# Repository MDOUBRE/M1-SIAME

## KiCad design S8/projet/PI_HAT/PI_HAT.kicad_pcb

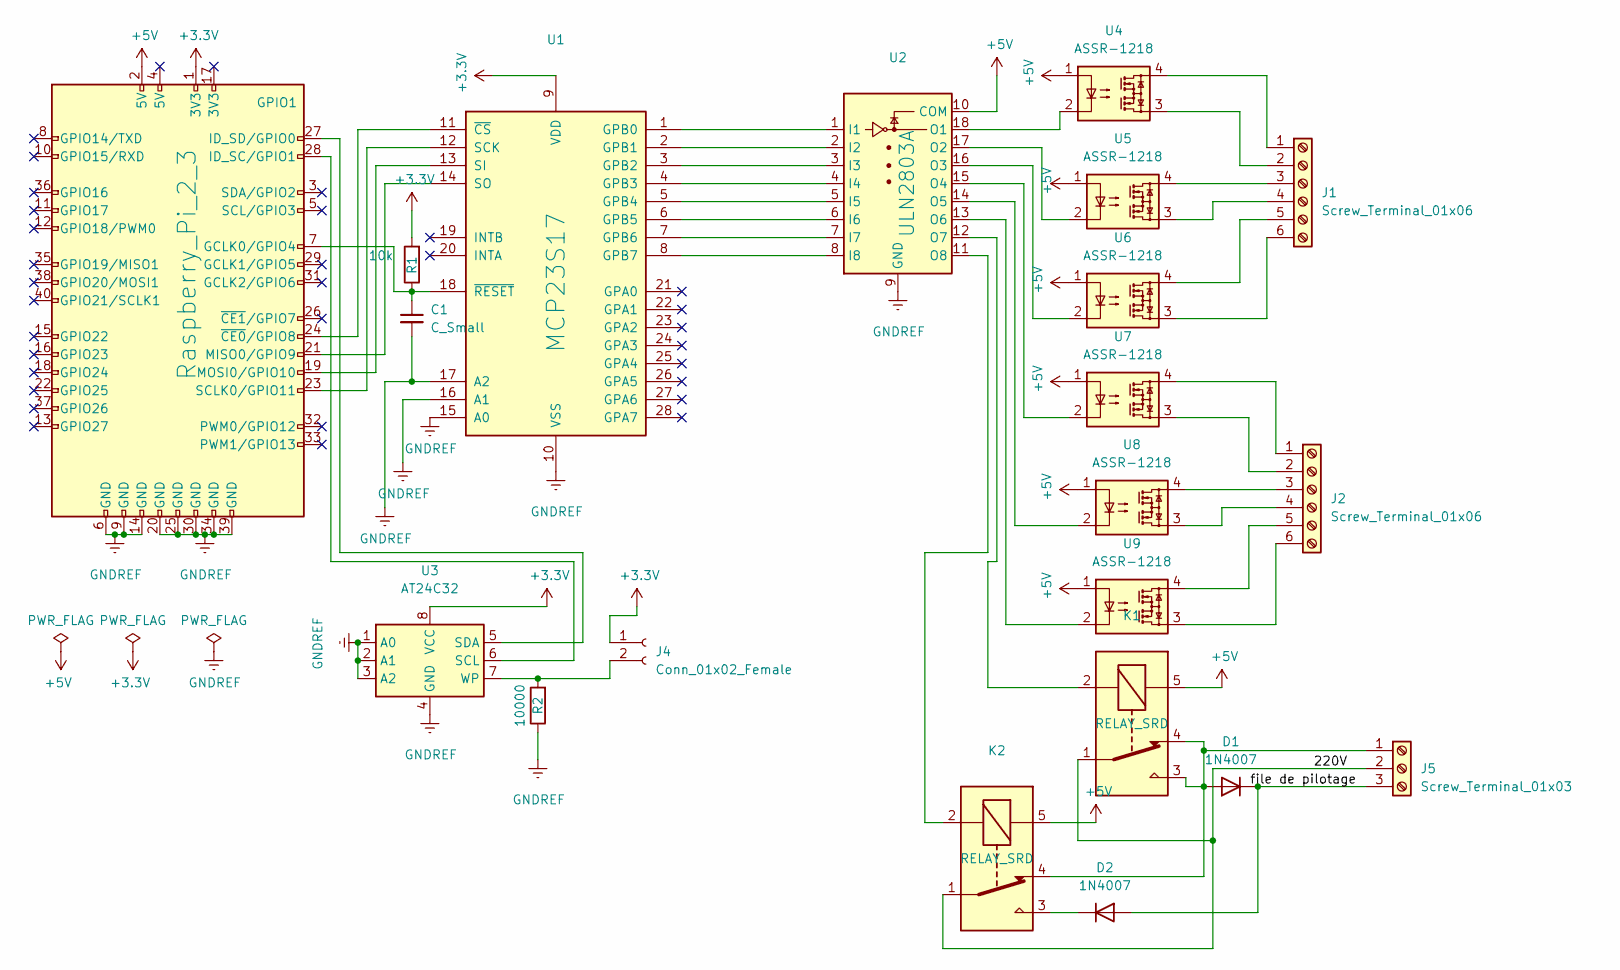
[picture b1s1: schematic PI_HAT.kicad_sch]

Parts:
C1: C_Small; CP_Elec_3x5.4
D1, D2: 1N4007; D_DO-41_SOD81_P10.16mm_Horizontal
GPIO1: Raspberry_Pi_2_3; PinSocket_2x20_P2.54mm_Vertical
J1, J2: Screw_Terminal_01x06; TerminalBlock_MetzConnect_Type086_RT03406HBLC_1x06_P3.81mm_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
J4: Conn_01x02_Female; PinHeader_1x02_P1.00mm_Horizontal
J5: Screw_Terminal_01x03; TerminalBlock_MetzConnect_Type086_RT03403HBLC_1x03_P3.81mm_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
K1, K2: RELAY_SRD; Relay_SPDT_SANYOU_SRD_Series_Form_C
R1: 10k; R_0805_2012Metric_Pad1.20x1.40mm_HandSolder
R2: 10000; R_0805_2012Metric_Pad1.20x1.40mm_HandSolder
U1: MCP23S17; DIP-28_W7.62mm_Socket
U2: ULN2803A; DIP-18_W7.62mm_Socket
U3: AT24C32; DIP-8_W7.62mm_Socket
U4, U5, U6, U7, U8, U9: ASSR-1218; SSR_AQG22105

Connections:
+3V3: GPIO1.1 (3V3), J4.1, R1.2, U1.9 (VDD), U3.8 (VCC)
+5V: GPIO1.2 (5V), K1.5, K2.5, U2.10 (COM), U4.1, U5.1, U6.1, U7.1, U8.1, U9.1
/220V: J5.2, K1.1, K2.1
/file de pilotage: D1.1 (K), D2.2 (A), J5.3
GNDREF: C1.2, GPIO1.6 (GND), GPIO1.9 (GND), GPIO1.14 (GND), GPIO1.20 (GND), GPIO1.25 (GND), GPIO1.30 (GND), GPIO1.34 (GND), GPIO1.39 (GND), R2.1, U1.10 (VSS), U1.15 (A0), U1.16 (A1), U1.17 (A2), U2.9 (GND), U3.1 (A0), U3.2 (A1), U3.3 (A2), U3.4 (GND)
unnamed: C1.1, GPIO1.7 (GCLK0/GPIO4), R1.1, U1.18 (~RESET~)
unnamed: GPIO1.19 (MOSI0/GPIO10), U1.13 (SI)
unnamed: GPIO1.21 (MISO0/GPIO9), U1.14 (SO)
unnamed: GPIO1.23 (SCLK0/GPIO11), U1.12 (SCK)
unnamed: GPIO1.24 (~CE0~/GPIO8), U1.11 (~CS~)
unnamed: GPIO1.27 (ID_SD/GPIO0), U3.5 (SDA)
unnamed: GPIO1.28 (ID_SC/GPIO1), U3.6 (SCL)
unnamed: J1.1, U4.4
unnamed: J1.2, U4.3
unnamed: J1.3, U5.4
unnamed: J1.4, U5.3
unnamed: J1.5, U6.4
unnamed: J1.6, U6.3
unnamed: J2.1, U7.4
unnamed: J2.2, U7.3
unnamed: J2.3, U8.4
unnamed: J2.4, U8.3
unnamed: J2.5, U9.4
unnamed: J2.6, U9.3
unnamed: J4.2, R2.2, U3.7 (WP)
unnamed: K1.2, U2.12 (O7)
unnamed: K2.2, U2.11 (O8)
unnamed: D2.1 (K), K2.3
unnamed: U1.1 (GPB0), U2.1 (I1)
unnamed: U1.2 (GPB1), U2.2 (I2)
unnamed: U1.3 (GPB2), U2.3 (I3)
unnamed: U1.4 (GPB3), U2.4 (I4)
unnamed: U1.5 (GPB4), U2.5 (I5)
unnamed: U1.6 (GPB5), U2.6 (I6)
unnamed: U1.7 (GPB6), U2.7 (I7)
unnamed: U1.8 (GPB7), U2.8 (I8)
unnamed: U2.13 (O6), U9.2
unnamed: U2.14 (O5), U8.2
unnamed: U2.15 (O4), U7.2
unnamed: U2.16 (O3), U6.2
unnamed: U2.17 (O2), U5.2
unnamed: U2.18 (O1), U4.2

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
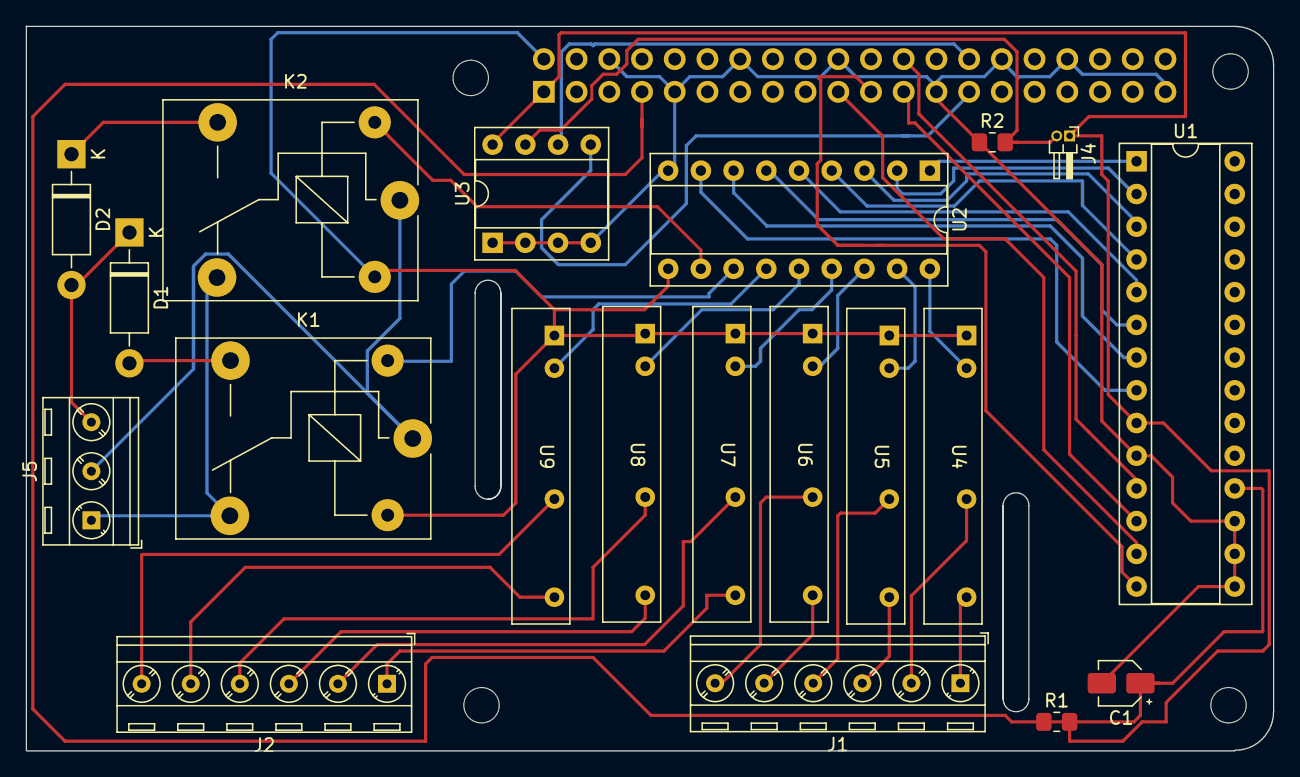
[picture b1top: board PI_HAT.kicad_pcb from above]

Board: 2 copper layers, 96.8 x 56.3 mm, 21 parts (1 on the bottom side), 44 nets.

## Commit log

2022-03-16 ajout de tout M1 ds M1-SIAME
2022-03-20 dezip de la phase 2 de la calculette C++
